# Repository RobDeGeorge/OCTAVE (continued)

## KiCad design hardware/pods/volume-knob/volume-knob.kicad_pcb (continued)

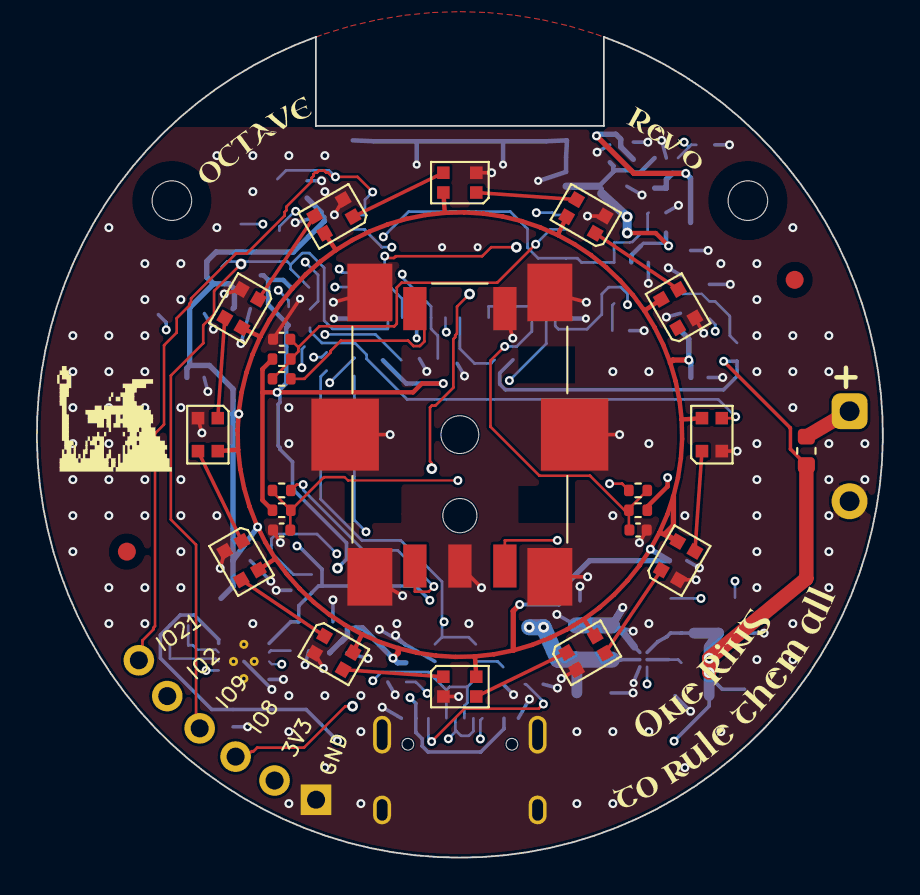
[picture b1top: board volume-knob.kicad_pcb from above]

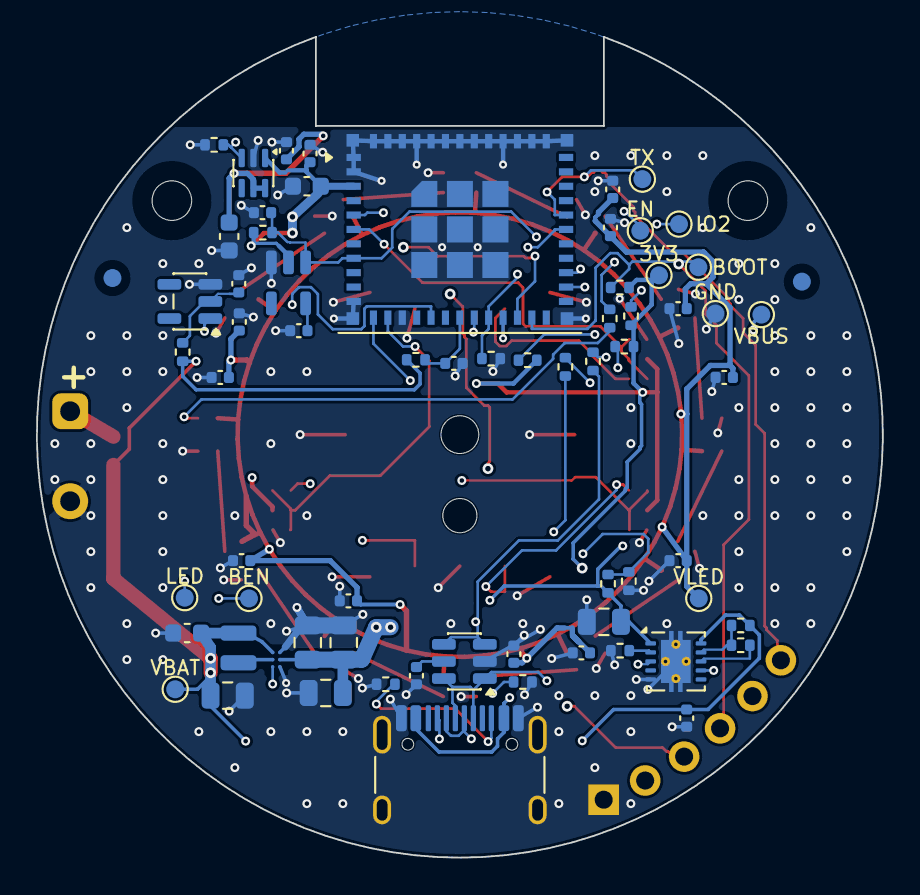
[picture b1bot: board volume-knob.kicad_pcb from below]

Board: 4 copper layers, 47.0 x 45.6 mm, 102 parts (75 on the bottom side), 49 nets.

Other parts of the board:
FID1, FID2, FID3, FID4: Fiducial_1mm_Mask2mm
H1, H2: M2; MountingHole_2.2mm_M2

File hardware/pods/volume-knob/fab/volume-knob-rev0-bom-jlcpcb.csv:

Comment,Designator,Footprint,LCSC
100n,"C1,C10,C13,C14,C19,C20,C21,C22,C23,C24,C25,C26,C27,C28,C29,C30",C_0402_1005Metric,C1525
4.7u,C2,C_0805_2012Metric,C1779
1u,"C3,C4",C_0402_1005Metric,C52923
10u,"C5,C11,C12",C_0603_1608Metric,C19702
22u,"C6,C7,C8,C9",C_0805_2012Metric,C45783
10n,"C15,C18",C_0402_1005Metric,C15195
220p,"C16,C17",C_0402_1005Metric,C1530
WS2812B-2020,"D1,D2,D3,D4,D5,D6,D7,D8,D9,D10,D11,D12",LED_WS2812B-2020_PLCC4_2.0x2.0mm,C52917434
3A,F1,Fuse_0603_1608Metric,C99558
USB-C,J1,USB_C_Receptacle_HRO_TYPE-C-31-M-12,C165948
1u,L1,L_Sunlord_SWPA252012S,C98348
5.1k,"R1,R2",R_0402_1005Metric,C25905
22,"R3,R4",R_0402_1005Metric,C25092
100k,"R5,R8,R10,R13",R_0402_1005Metric,C25741
150k,R6,R_0402_1005Metric,C25755
2k,R7,R_0402_1005Metric,C4109
200k,R9,R_0402_1005Metric,C25764
10k,"R11,R14,R15,R16,R17,R18",R_0402_1005Metric,C25744
470k,R12,R_0402_1005Metric,C25790
1k,"R19,R21,R23",R_0402_1005Metric,C11702
1M,"R20,R22",R_0402_1005Metric,C26083
33k,R24,R_0402_1005Metric,C25779
330,R25,R_0402_1005Metric,C25104
EC11J1525402,SW1,RotaryEncoder_Alps_EC11J15_SMD,C209762
USBLC6-2SC6,U1,SOT-23-6,C7519
BQ25173QWDRCRQ1,U2,Texas_DRC0010J_ThermalVias,C20345235
TPS3840PL16DBVR,U3,SOT-23-5,C1852124
TPS61299YBHR,U4,TI_YBH0006_WCSP-6_0.8x1.2mm,C20882919
TPS22919DCKR,U5,SOT-363_SC-70-6,C2149796
ESP32-C3-MINI-1-H4X,U6,ESP32-C3-MINI-1,C41349510
TPS3840DL28DBVR,U7,SOT-23-5,C2066416

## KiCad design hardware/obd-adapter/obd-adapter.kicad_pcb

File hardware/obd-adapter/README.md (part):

# OCTAVE OBD adapter, Rev 0 (bring-up board)

Our own OBD-II adapter: STM32G474 (vehicle side) + ESP32 (Bluetooth Classic SPP, BLE, Wi-Fi), every OBD-II bus, USB-C. Rev 0 is a bring-up board for the bench and the Jeep, not the final dongle. It has room to probe, test points and header access to spare pins, and it plugs straight into the car's OBD-II port. Plan and background: `TODO/diy-obd-adapter.md`.

**Status:** generated, then verified: an STM32 pin check against ST's pin data, two independent datasheet audits and ngspice simulations. Every finding is fixed or accepted, see `verify/REVIEW.md`. Not yet reviewed by a human, not ordered. Read "Before ordering" below.

**Compact two-sided board, after four design reviews (2026-11-24 and 25): routed, order files in `fab/`, not reviewed by a person, not ordered.** The board is **80 x 55 mm, six layers, parts on both sides** (74 on top, 144 underneath, 218 in all; 205 fitted by JLCPCB): 86 % of the area of the first compact pass (89 x 57.5 mm) and 60 % of the one-sided 100 x 70 mm board with its pod-bus lobe.

- **Routed and rule-checked:** 0 unconnected pads, 0 errors, schematic and board agree (ERC 0 / 0). Eight DRC warnings are left: silkscreen outlines over the board edge (the USB-C socket's twice, the module's once), U4's footprint differing from the library copy on purpose (1), and four vias KiCad calls dangling (each joins tracks of one layer; the clean-up step leaves any whose removal would open a net). `gen/routing.json` is this route and `build.py route` replays it.
- **Six layers** (F.Cu signal, In1 GND, In2 signal, In3 signal, In4 3V3, B.Cu signal). 292 signal vias of 0.45 / 0.2 mm, 305 of 0.6 / 0.3 mm. **Six layers and two-sided assembly cost more than Rev 0 would have; neither is priced.**
- **0402 for the logic-level resistors and small capacitors** (`HV_NETS` in `gen/obd_adapter.py` says which nets keep 0603: everything that can see the battery or a bus line, the buck's own parts, the 0.1 % divider, 4.7 µF and 10 µF). 0402 was estimated to get the board to 80 x 50 mm; it gets it to 80 x 55, because the chips, diodes, transistors and connectors are what fill the back, and 0402 shrinks none of them.
- **One USB-C port for both chips:** a hub (U18 CH334P, Y2), the CH340C (U14) with its auto-reset pair on the hub's second port; one RGB LED (D1) in place of three; the four ESP32 programming pads are gone.
- **Changed by the design review of 2026-11-24** (three reviews: circuit, copper, manufacturing; what each found is in the next section).
- **`fab/` is this board** (`build.py fab`, 2026-11-25): gerbers, BOM, placement file for both sides, and the plug adapter's gerbers with its anchoring holes. The placement file's angles are checked against JLCPCB's own footprints for all but the inductor (see "What an order still needs"); the route of 2026-11-25 (after the fourth review's changes) is itself not reviewed.
- **Not re-verified:** `verify/REVIEW.md`, the pin check and the simulations describe the Rev 0 layout and netlist. Nothing added on 2026-11-24 is simulated.
- **Sections below "Blocks"** partly still describe the Rev 0 layout: "Before ordering" and "Known Rev 0 limits" have not been rewritten for the compact board.

## Design review of 2026-11-24

Three independent reviews of the routed board (circuit against datasheets; the copper, measured; manufacturing and the plug joint). What they found and what was done:

**Fixed in the netlist**
- **USB ESD array's clamp pin (U2 pin 5) is on 3V3, not VBUS.** On VBUS, the hub's D+ pull-up fed the cable-less VBUS through the array: about 1 mA while parked, and enough on the ESP32 load switch's ON pin to turn the ESP32 on in a warm car.
- **Pod supply switch: U19 TPS27S100A** (HTSSOP-14) replaces the discrete P-FET switch (Q12, Q13, R71, D29 are gone; C52 and R72 have new jobs). It limits at 0.82 A (R72 3k; 0.59-1.05 A over tolerance and temperature), shuts down hot and retries. The P-FET would have burned in a shorted pod cable before the polyfuse tripped. **A shorted cable is survived, not free:** U19 then cycles at its thermal limit and draws about 0.2 A from the battery for as long as it is on, under the polyfuse's hold current, and its fault flag is not wired (no pin left). Firmware must switch `POD_EN` off when the pods stop answering and when the car is parked. U19 is rated 40 V, 48 V for 0.4 s.
- **Input TVS: 5.0SMDJ33CA** (it was 26CA). The 26 V part breaks down at 28.9-31.9 V, so it conducted through the whole of a clamped load dump (35 V, up to 0.4 s). The 33 V part starts at 36.7 V and clamps higher: about 42 V at 10 A and 46 V at 43 A at 25 °C, an estimated 49 to 50 V hot. That is at the rating of the 50 V capacitors and 1 to 2 V over U19's 48 V transient rating in the worst pulse in a hot car; accepted. **The LM317L (U11) is behind its own 30 V clamp** (Q15 BCX56-16 in SOT-89 as an emitter follower, D31 30 V zener, R80 1k): a firmware rule could not have protected it from a pulse that rises in a microsecond. The follower costs 0.7 to 1.5 V: Bus+ falls under VPW's 6.25 V when the plug is under about 9.0 V (10.8 V at worst, cold); without it 8.2 / 9.3 V. With Bus+ shorted while the adapter transmits, the LM317L's current limit flows through Q15, about 1 W: the SOT-89 takes that for a while, and **firmware must stop transmitting when `VPW_RX` does not echo the bus going high.** The comparator supply's resistor R43 is 1k (it was 470 Ω), so its 33 V zener stays inside its rating at the 41 V the TVS can let by for 0.4 s.
- **Q14: CONFIG switch 4 (BOOT0) also holds the ESP32 in reset,** and R78 holds the ESP32's TX line idle meanwhile. A USB cable powers the ESP32 by itself now, and one byte from it while the STM32's ROM bootloader picks its interface kept DFU from enumerating.
- **D30, a 5.1 V zener on the panic input:** the ESD diode alone lets PC13 reach 5 to 7 V with the cable shorted to the battery. R66 is 2k in 1206: 4.5 mA into the zener at 14.4 V (5.36 V at most), about 5.6 V at a 28 V jump start.
- **10 µF and 100 nF at the hub** (C55, C58): its low-voltage reset is 3.15 V at worst (datasheet V2.91: 2.6 / 3.0 / 3.15 V), the LDO 3.25 V before a load step, so the static margin is 100 mV; 3.15 V is also the hub's lowest operating voltage. **Check on the first board with Wi-Fi transmitting.** If the hub resets, it needs a small regulator of its own from 5V (its V5 pin cannot take 5V directly: on USB power that rail is 4.0 to 4.6 V, under the pin's 4.5 V minimum).

**Fixed in the copper** (`gen/prewire.py`, `gen/pcbgen.py`, `gen/build.py`)
- **`VBAT_P` leaves the ideal-diode FET on a 1.0 mm trunk** to the buck, the 10 µF and the 47 µF, with a via for the branches. Everything behind the FET had hung on the LM74700's 0.4 mm sense track and one via.
- **No fan-out via in a pad** (there were 20, under the STM32's pins and the accelerometer among them), none in a signal pin's way out of a fine-pitch chip, none in the USB-C shell's slot. The hub's centre pad has four vias in it on purpose, and about a dozen vias of a pad's own net stand 0.05 to 0.09 mm beside it (the buck's hand-laid ground vias, the module's ground pad, a few others). **Order the board with filled and capped vias.**
- **Beside the plug's hand-soldered pads:** no via and no pour within 0.45 mm of the pads on either side, no pour under the PTC, the PTC's battery pad 1.2 mm from the pads (0.65 before), 0.6 mm clearance round the unfused `VBAT_IN` copper (0.3 before).
- **Each CAN transceiver's 5 V capacitor is wired straight to its VCC pin;** the pod supply runs 0.6 mm on the outer layers (0.3 mm on an inner layer before); four ground vias under the hub; three to four more ground vias at the plug's ground pins, the TVS and the 47 µF.
- **No battery-side net on the top layer under the ESP32 module** (measured on this route: none).
- **The high-speed USB pair is laid by hand** (`gen/prewire.py`): socket, ESD array, hub, on B.Cu but for 2 mm at the socket, 21.5 and 22.0 mm long, three vias in all, the two lines 0.2 to 0.6 mm apart. Its impedance is not designed (0.15 mm tracks over the 3V3 plane, about 100 Ω differential by estimate). The STM32 is on the hub's port 3 now, so the upstream pins have their side of the chip alone.
- **Both CAN transceivers have their own 5 V feed** from the OR diode's anode, down In2 beside the feedback-sense trace, to a via at each one's 5 V capacitor. (The J1850 pull-up and reference divider, under 1 mA together, may still join the sense trace.)
- **The plug's two ground pins have four vias** on a short bus beside them, laid by hand; the LM317L's input capacitor is wired straight to its input pin; the pod switch's exposed pad has six vias into the ground plane; VBUS may use the inner layers (kept to the outer ones it ran 145 mm round the board); the pod output is 0.6 mm on the outer layers and the pod input 0.6 mm throughout (36 mm of it on an inner layer, where the finisher put it); the ESP32's supply pin has a via straight down to its 100 nF.
- **Track ends are welded** onto the track they join: the finisher had left 16 joints held only by overlapping round ends, narrower than a track.
- **The plug adapter board has two plated 0.45 mm holes in each joint pad,** at the end where pulling the plug out starts to peel it. (The main board's pads cannot have them: pin n and pin n + 8 are back to back.)

**Left as it is, on purpose or for now**
- **The joint still needs epoxy or a case that clamps the plug and the board.** The fillets were estimated to start lifting near 42 N; a J1962 plug takes 20 to 90 N to pull. Never pull the adapter out by its board. Treat the bead of epoxy along the joint as required.
- **The four buttons stand 5.7 mm apart:** a fingertip presses two. That is the price of the 80 mm length.
- **The battery-side clearance of 0.3 mm does not apply to `VJ1850` (7.2 V, regulated) and `K_IN` (behind 10k):** with it, the corner where the J1850 regulator stands over the comparator could not be wired.
- **The RGB LED's green and blue may be swapped:** its datasheet drawing has pin 3 green and pin 4 blue, as wired; JLCPCB's symbol for the same part number has them the other way round. A firmware swap if so.
- **The hub's D+ pull-up is always on** (the CH334P has no cable-detect pin): a cable to a powered-off host back-drives its D+ with up to 1.8 mA while parked.
- **The 3.3 V LDO** dissipates about 0.6 W with Wi-Fi sustained; in a hot car it may reach its thermal shutdown, which resets the board. Measure its tab on the first board.
- **The STM32 cannot tell that a USB cable is in** (no pin left): firmware polls, or stays attached at 0.1 mA from the battery.
- **Silkscreen outlines stand closer than 0.15 mm to their own part's pads** in about 300 places (the library's drawings); JLCPCB trims them.

## Design review of 2026-11-25 (fourth round)

Three more independent reviews (circuit, the copper of the route of that morning, the order package). No blocker in the circuit or the copper; one in the placement file. What was done:

- **Q15's placement angle was 180 degrees out** and its reel (C549696) had 4 pieces: it is the same part on the other reel now (C100026, BCX56-16,115) with its own correction. Every other part number's angle was confirmed against JLCPCB's footprint, J11 moved 0.25 mm.
- **The DLC switch is in the corner behind the buck's input,** under the copper it switches from: one via up into `VBAT_P`. It stood under the ESP32 module, and `VBAT_P` and `DLC_SW` crossed the board to it and back: 95 and 112 mm of battery-side track under the reset button, the STM32 and its crystal. The wizard has its old place.
- **Q15 has copper:** four vias in its collector tab to a patch on the top side (about 0.25 cm2, all there is room for). On the bare pad it was good for 0.5 W; the fault it has to stand (Bus+ shorted while transmitting) is 0.4 W typical, 1.4 W at worst. **Still a firmware obligation:** stop transmitting when `VPW_RX` does not echo.
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
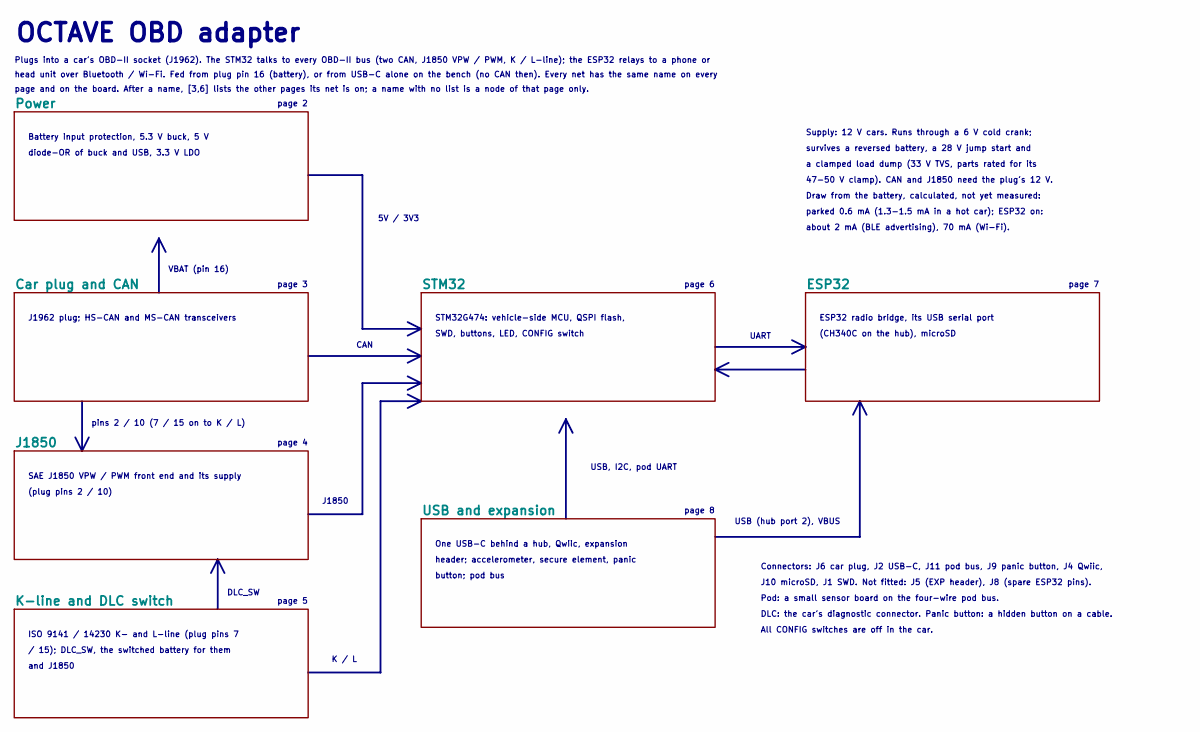
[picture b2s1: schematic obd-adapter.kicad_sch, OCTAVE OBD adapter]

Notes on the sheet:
page 2
Battery input protection, 5.3 V buck, 5 V
diode-OR of buck and USB, 3.3 V LDO
page 3
J1962 plug; HS-CAN and MS-CAN transceivers
page 4
SAE J1850 VPW / PWM front end and its supply
(plug pins 2 / 10)
page 5
ISO 9141 / 14230 K- and L-line (plug pins 7
/ 15); DLC_SW, the switched battery for them
and J1850
page 6
STM32G474: vehicle-side MCU, QSPI flash,
SWD, buttons, LED, CONFIG switch
page 7
ESP32 radio bridge, its USB serial port
(CH340C on the hub), microSD
page 8
One USB-C behind a hub, Qwiic, expansion
header; accelerometer, secure element, panic
button; pod bus
VBAT (pin 16)
5V / 3V3
CAN
J1850
K / L
UART
USB, I2C, pod UART
USB (hub port 2), VBUS
pins 2 / 10 (7 / 15 on to K / L)
DLC_SW
Connectors: J6 car plug, J2 USB-C, J11 pod bus, J9 panic button, J4 Qwiic,
J10 microSD, J1 SWD. Not fitted: J5 (EXP header), J8 (spare ESP32 pins).
Pod: a small sensor board on the four-wire pod bus.
DLC: the car's diagnostic connector. Panic button: a hidden button on a cable.
All CONFIG switches are off in the car.
Supply: 12 V cars. Runs through a 6 V cold crank;
survives a reversed battery, a 28 V jump start and
a clamped load dump (33 V TVS, parts rated for its

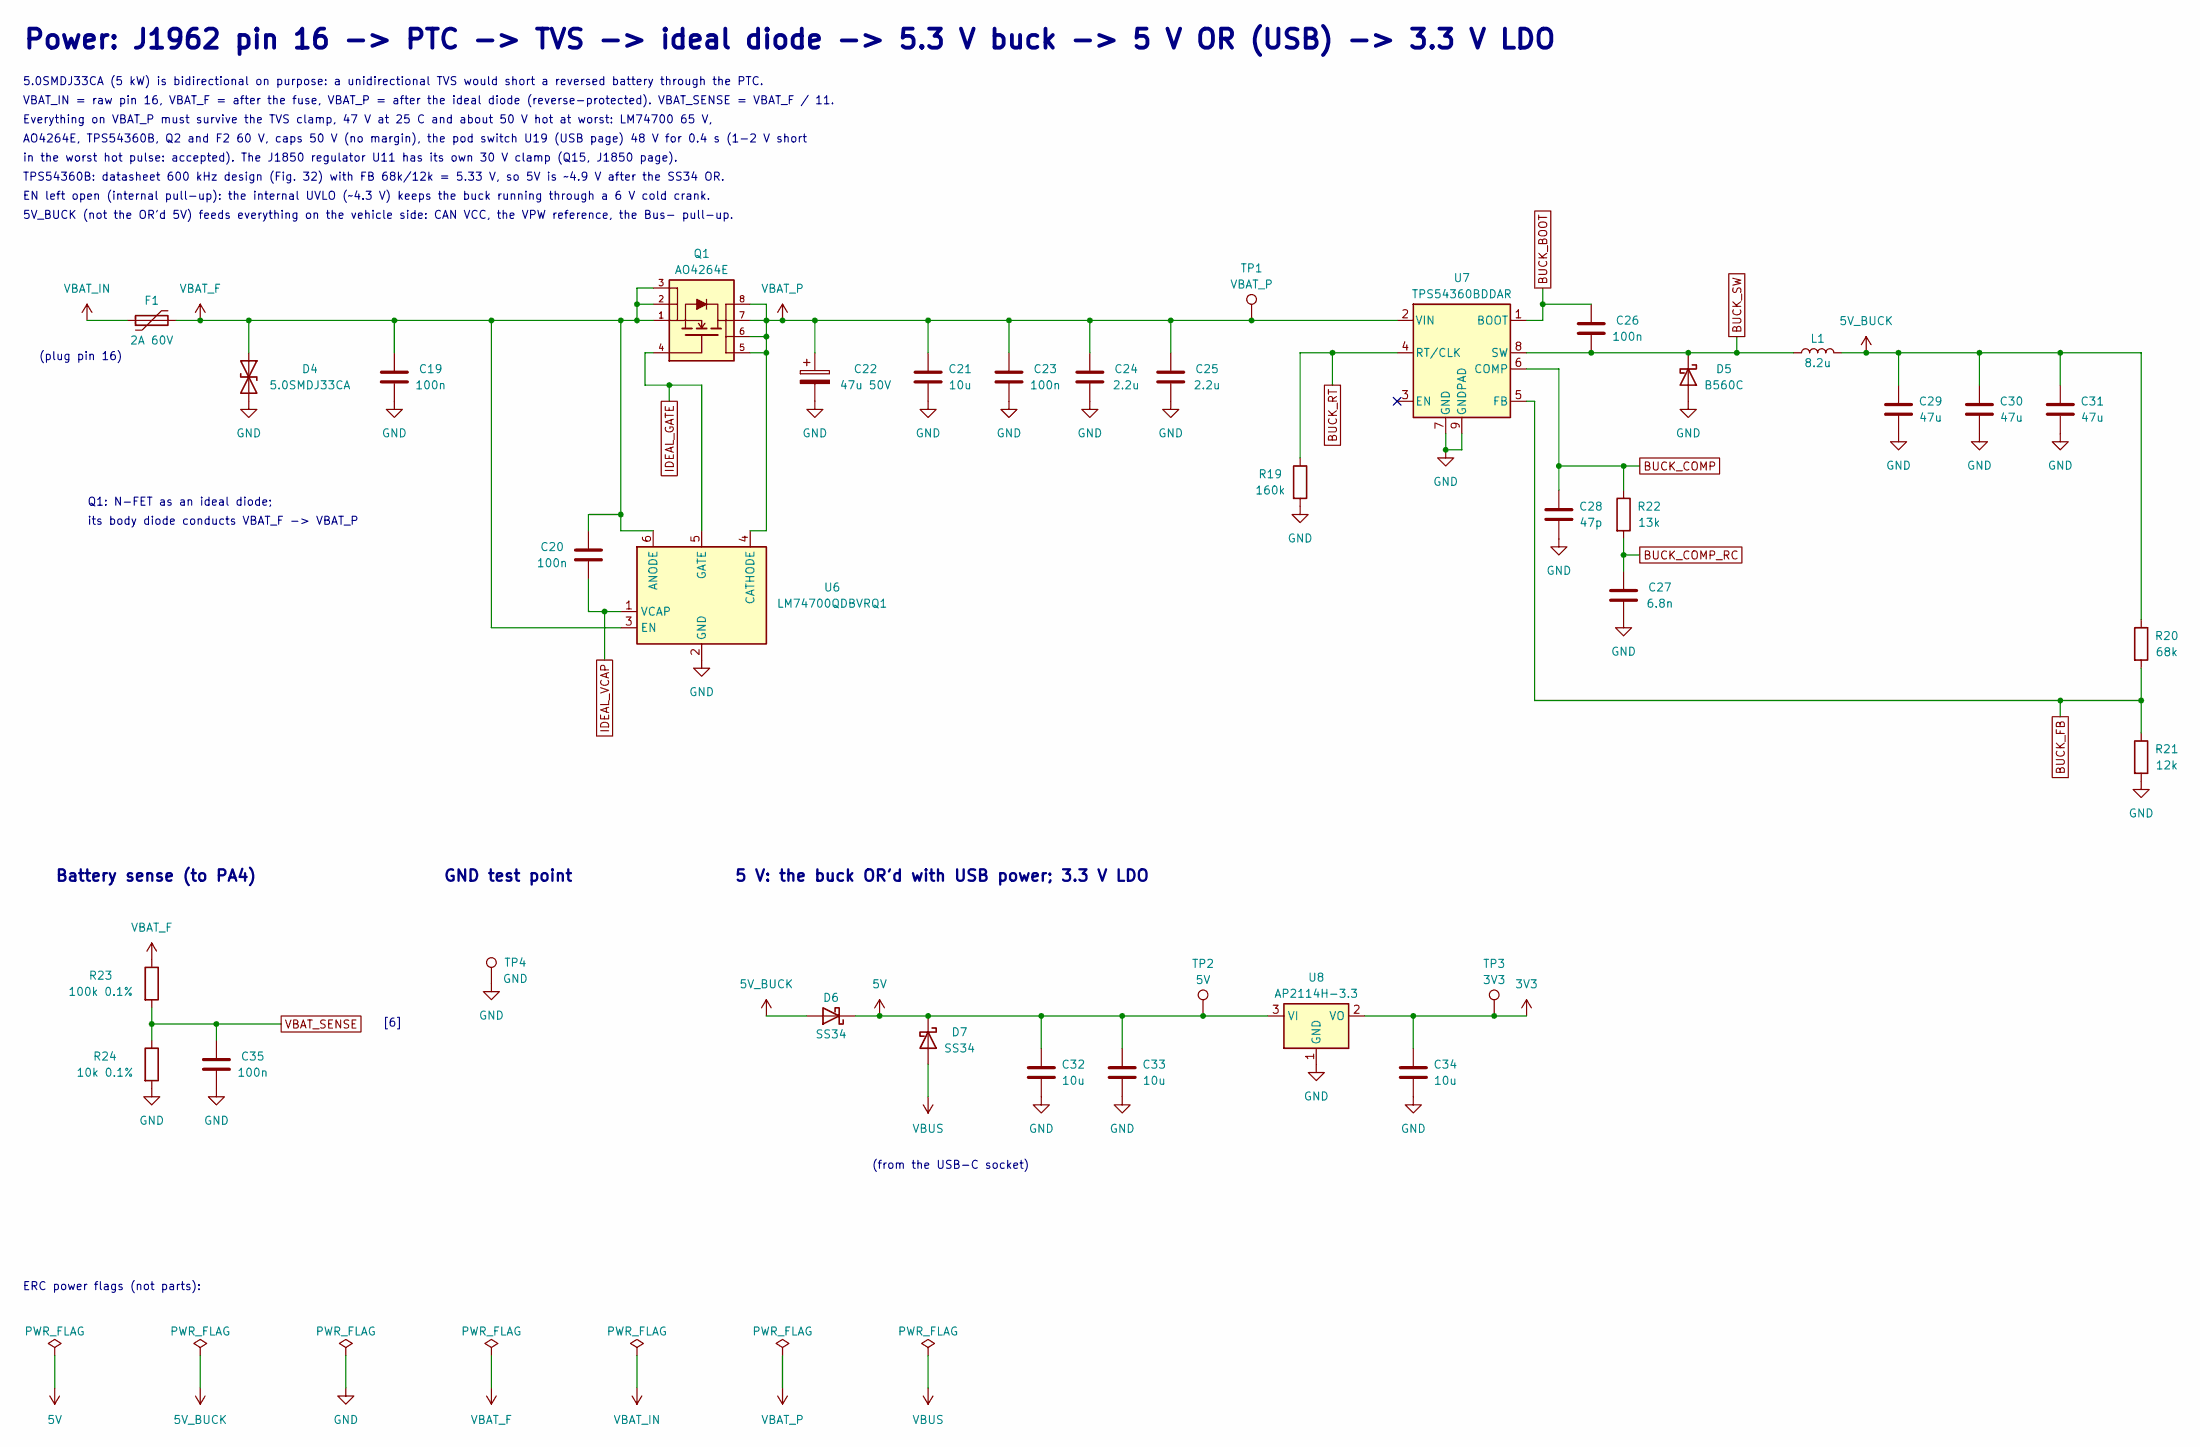
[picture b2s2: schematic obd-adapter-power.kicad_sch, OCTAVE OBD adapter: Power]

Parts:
C19, C20, C23, C26: 100n; C_0603_1608Metric; LCSC C14663
C21: 10u; C_1206_3216Metric; LCSC C13585
C22: 47u 50V; CP_Elec_6.3x7.7; LCSC C2887275
C24, C25: 2.2u; C_1206_3216Metric; LCSC C50254
C27: 6.8n; C_0603_1608Metric; LCSC C1631
C28: 47p; C_0603_1608Metric; LCSC C1671
C29, C30, C31: 47u; C_1206_3216Metric; LCSC C96123
C32, C33, C34: 10u; C_0603_1608Metric; LCSC C96446
C35: 100n; C_0402_1005Metric; LCSC C307331
D4: 5.0SMDJ33CA; D_SMC; LCSC C2913642
D5: B560C; D_SMC; LCSC C85100
D6, D7: SS34; D_SMA; LCSC C8678
F1: 2A 60V; Fuse_2920_7451Metric; LCSC C49326266
L1: 8.2u; L_Changjiang_FNR8065S; LCSC C96978
Q1: AO4264E; SOIC-8_3.9x4.9mm_P1.27mm; LCSC C334232
R19: 160k; R_0603_1608Metric; LCSC C22813
R20: 68k; R_0603_1608Metric; LCSC C23231
R21: 12k; R_0603_1608Metric; LCSC C22790
R22: 13k; R_0603_1608Metric; LCSC C22797
R23: 100k 0.1%; R_0603_1608Metric; LCSC C122538
R24: 10k 0.1%; R_0603_1608Metric; LCSC C95204
TP1: VBAT_P; TestPoint_Pad_D1.5mm
TP2: 5V; TestPoint_Pad_D1.5mm
TP3: 3V3; TestPoint_Pad_D1.5mm
TP4: GND; TestPoint_Pad_D1.5mm
U6: LM74700QDBVRQ1; SOT-23-6; LCSC C2941042
U7: TPS54360BDDAR; TI_SO-PowerPAD-8_ThermalVias; LCSC C524806
U8: AP2114H-3.3; SOT-223-3_TabPin2; LCSC C150716

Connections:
3V3: C34.1, TP3.1, U8.2 (VO); also elsewhere on the board
5V: C32.1, C33.1, D6.1 (K), D7.1 (K), TP2.1, U8.3 (VI); also elsewhere on the board
5V_BUCK: C29.1, C30.1, C31.1, D6.2 (A), L1.2, R20.1; also elsewhere on the board
BUCK_BOOT: C26.1, U7.1 (BOOT)
BUCK_COMP: C28.1, R22.1, U7.6 (COMP)
BUCK_COMP_RC: C27.1, R22.2
BUCK_FB: R20.2, R21.1, U7.5 (FB)
BUCK_RT: R19.1, U7.4 (RT/CLK)
BUCK_SW: C26.2, D5.1 (K), L1.1, U7.8 (SW)
GND: C19.2, C21.2, C22.2, C23.2, C24.2, C25.2, C27.2, C28.2, C29.2, C30.2, C31.2, C32.2, C33.2, C34.2, C35.2, D4.2 (A2), D5.2 (A), R19.2, R21.2, R24.2, TP4.1, U6.2 (GND), U7.7 (GND), U7.9 (GNDPAD), U8.1 (GND); also elsewhere on the board
IDEAL_GATE: Q1.4 (G), U6.5 (GATE)
IDEAL_VCAP: C20.1, U6.1 (VCAP)
VBAT_F: C19.1, C20.2, D4.1 (A1), F1.2, Q1.1 (S), Q1.2 (S), Q1.3 (S), R23.1, U6.3 (EN), U6.6 (ANODE)
VBAT_IN: F1.1; also elsewhere on the board
VBAT_P: C21.1, C22.1, C23.1, C24.1, C25.1, Q1.5 (D), Q1.6 (D), Q1.7 (D), Q1.8 (D), TP1.1, U6.4 (CATHODE), U7.2 (VIN); also elsewhere on the board
VBAT_SENSE: C35.1, R23.2, R24.1; also elsewhere on the board
VBUS: D7.2 (A); also elsewhere on the board

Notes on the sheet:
ERC power flags (not parts):
Power: J1962 pin 16 -> PTC -> TVS -> ideal diode -> 5.3 V buck -> 5 V OR (USB) -> 3.3 V LDO
5.0SMDJ33CA (5 kW) is bidirectional on purpose: a unidirectional TVS would short a reversed battery through the PTC.
VBAT_IN = raw pin 16, VBAT_F = after the fuse, VBAT_P = after the ideal diode (reverse-protected). VBAT_SENSE = VBAT_F / 11.
Everything on VBAT_P must survive the TVS clamp, 47 V at 25 C and about 50 V hot at worst: LM74700 65 V,
AO4264E, TPS54360B, Q2 and F2 60 V, caps 50 V (no margin), the pod switch U19 (USB page) 48 V for 0.4 s (1-2 V short
in the worst hot pulse: accepted). The J1850 regulator U11 has its own 30 V clamp (Q15, J1850 page).
TPS54360B: datasheet 600 kHz design (Fig. 32) with FB 68k/12k = 5.33 V, so 5V is ~4.9 V after the SS34 OR.
EN left open (internal pull-up): the internal UVLO (~4.3 V) keeps the buck running through a 6 V cold crank.
5V_BUCK (not the OR'd 5V) feeds everything on the vehicle side: CAN VCC, the VPW reference, the Bus- pull-up.
(plug pin 16)
Q1: N-FET as an ideal diode;
its body diode conducts VBAT_F -> VBAT_P
5 V: the buck OR'd with USB power; 3.3 V LDO
(from the USB-C socket)
Battery sense (to PA4)
GND test point
[6]

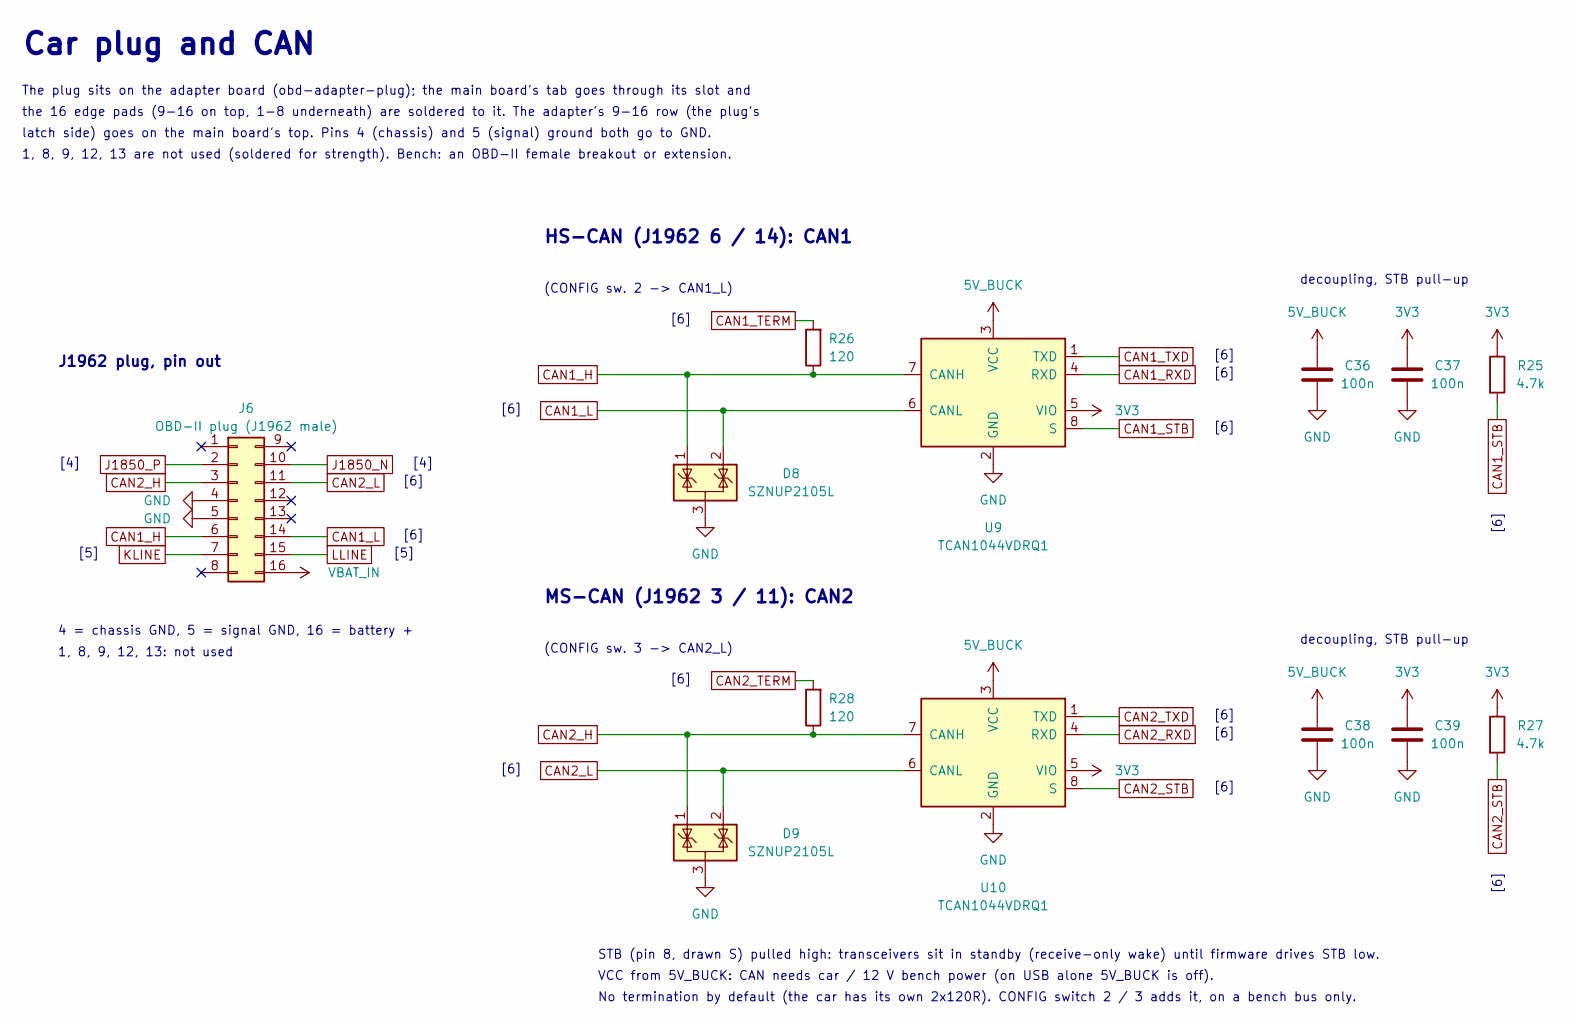
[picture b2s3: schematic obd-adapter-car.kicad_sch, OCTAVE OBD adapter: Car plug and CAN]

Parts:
C36, C37, C38, C39: 100n; C_0402_1005Metric; LCSC C307331
D8, D9: SZNUP2105L; SOT-23; LCSC C233494
J6: OBD-II plug (J1962 male); J1962_Edge_Joint
R25, R27: 4.7k; R_0402_1005Metric; LCSC C25900
R26, R28: 120; R_0603_1608Metric; LCSC C22787
U9, U10: TCAN1044VDRQ1; SOIC-8_3.9x4.9mm_P1.27mm; LCSC C1852061

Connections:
3V3: C37.1, C39.1, R25.1, R27.1, U9.5 (VIO), U10.5 (VIO); also elsewhere on the board
5V_BUCK: C36.1, C38.1, U9.3 (VCC), U10.3 (VCC); also elsewhere on the board
CAN1_H: D8.1 (K), J6.6, R26.1, U9.7 (CANH)
CAN1_L: D8.2 (K), J6.14, U9.6 (CANL); also elsewhere on the board
CAN1_RXD: U9.4 (RXD); also elsewhere on the board
CAN1_STB: R25.2, U9.8 (S); also elsewhere on the board
CAN1_TERM: R26.2; also elsewhere on the board
CAN1_TXD: U9.1 (TXD); also elsewhere on the board
CAN2_H: D9.1 (K), J6.3, R28.1, U10.7 (CANH)
CAN2_L: D9.2 (K), J6.11, U10.6 (CANL); also elsewhere on the board
CAN2_RXD: U10.4 (RXD); also elsewhere on the board
CAN2_STB: R27.2, U10.8 (S); also elsewhere on the board
CAN2_TERM: R28.2; also elsewhere on the board
CAN2_TXD: U10.1 (TXD); also elsewhere on the board
GND: C36.2, C37.2, C38.2, C39.2, D8.3 (A), D9.3 (A), J6.4, J6.5, U9.2 (GND), U10.2 (GND); also elsewhere on the board
J1850_N: J6.10; also elsewhere on the board
J1850_P: J6.2; also elsewhere on the board
KLINE: J6.7; also elsewhere on the board
LLINE: J6.15; also elsewhere on the board
VBAT_IN: J6.16; also elsewhere on the board

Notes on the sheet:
Car plug and CAN
The plug sits on the adapter board (obd-adapter-plug); the main board's tab goes through its slot and
the 16 edge pads (9-16 on top, 1-8 underneath) are soldered to it. The adapter's 9-16 row (the plug's
latch side) goes on the main board's top. Pins 4 (chassis) and 5 (signal) ground both go to GND.
1, 8, 9, 12, 13 are not used (soldered for strength). Bench: an OBD-II female breakout or extension.
J1962 plug, pin out
4 = chassis GND, 5 = signal GND, 16 = battery +
1, 8, 9, 12, 13: not used
HS-CAN (J1962 6 / 14): CAN1
(CONFIG sw. 2 -> CAN1_L)
decoupling, STB pull-up
MS-CAN (J1962 3 / 11): CAN2
(CONFIG sw. 3 -> CAN2_L)
STB (pin 8, drawn S) pulled high: transceivers sit in standby (receive-only wake) until firmware drives STB low.
VCC from 5V_BUCK: CAN needs car / 12 V bench power (on USB alone 5V_BUCK is off).
No termination by default (the car has its own 2x120R). CONFIG switch 2 / 3 adds it, on a bench bus only.
[4]
[5]
[6]

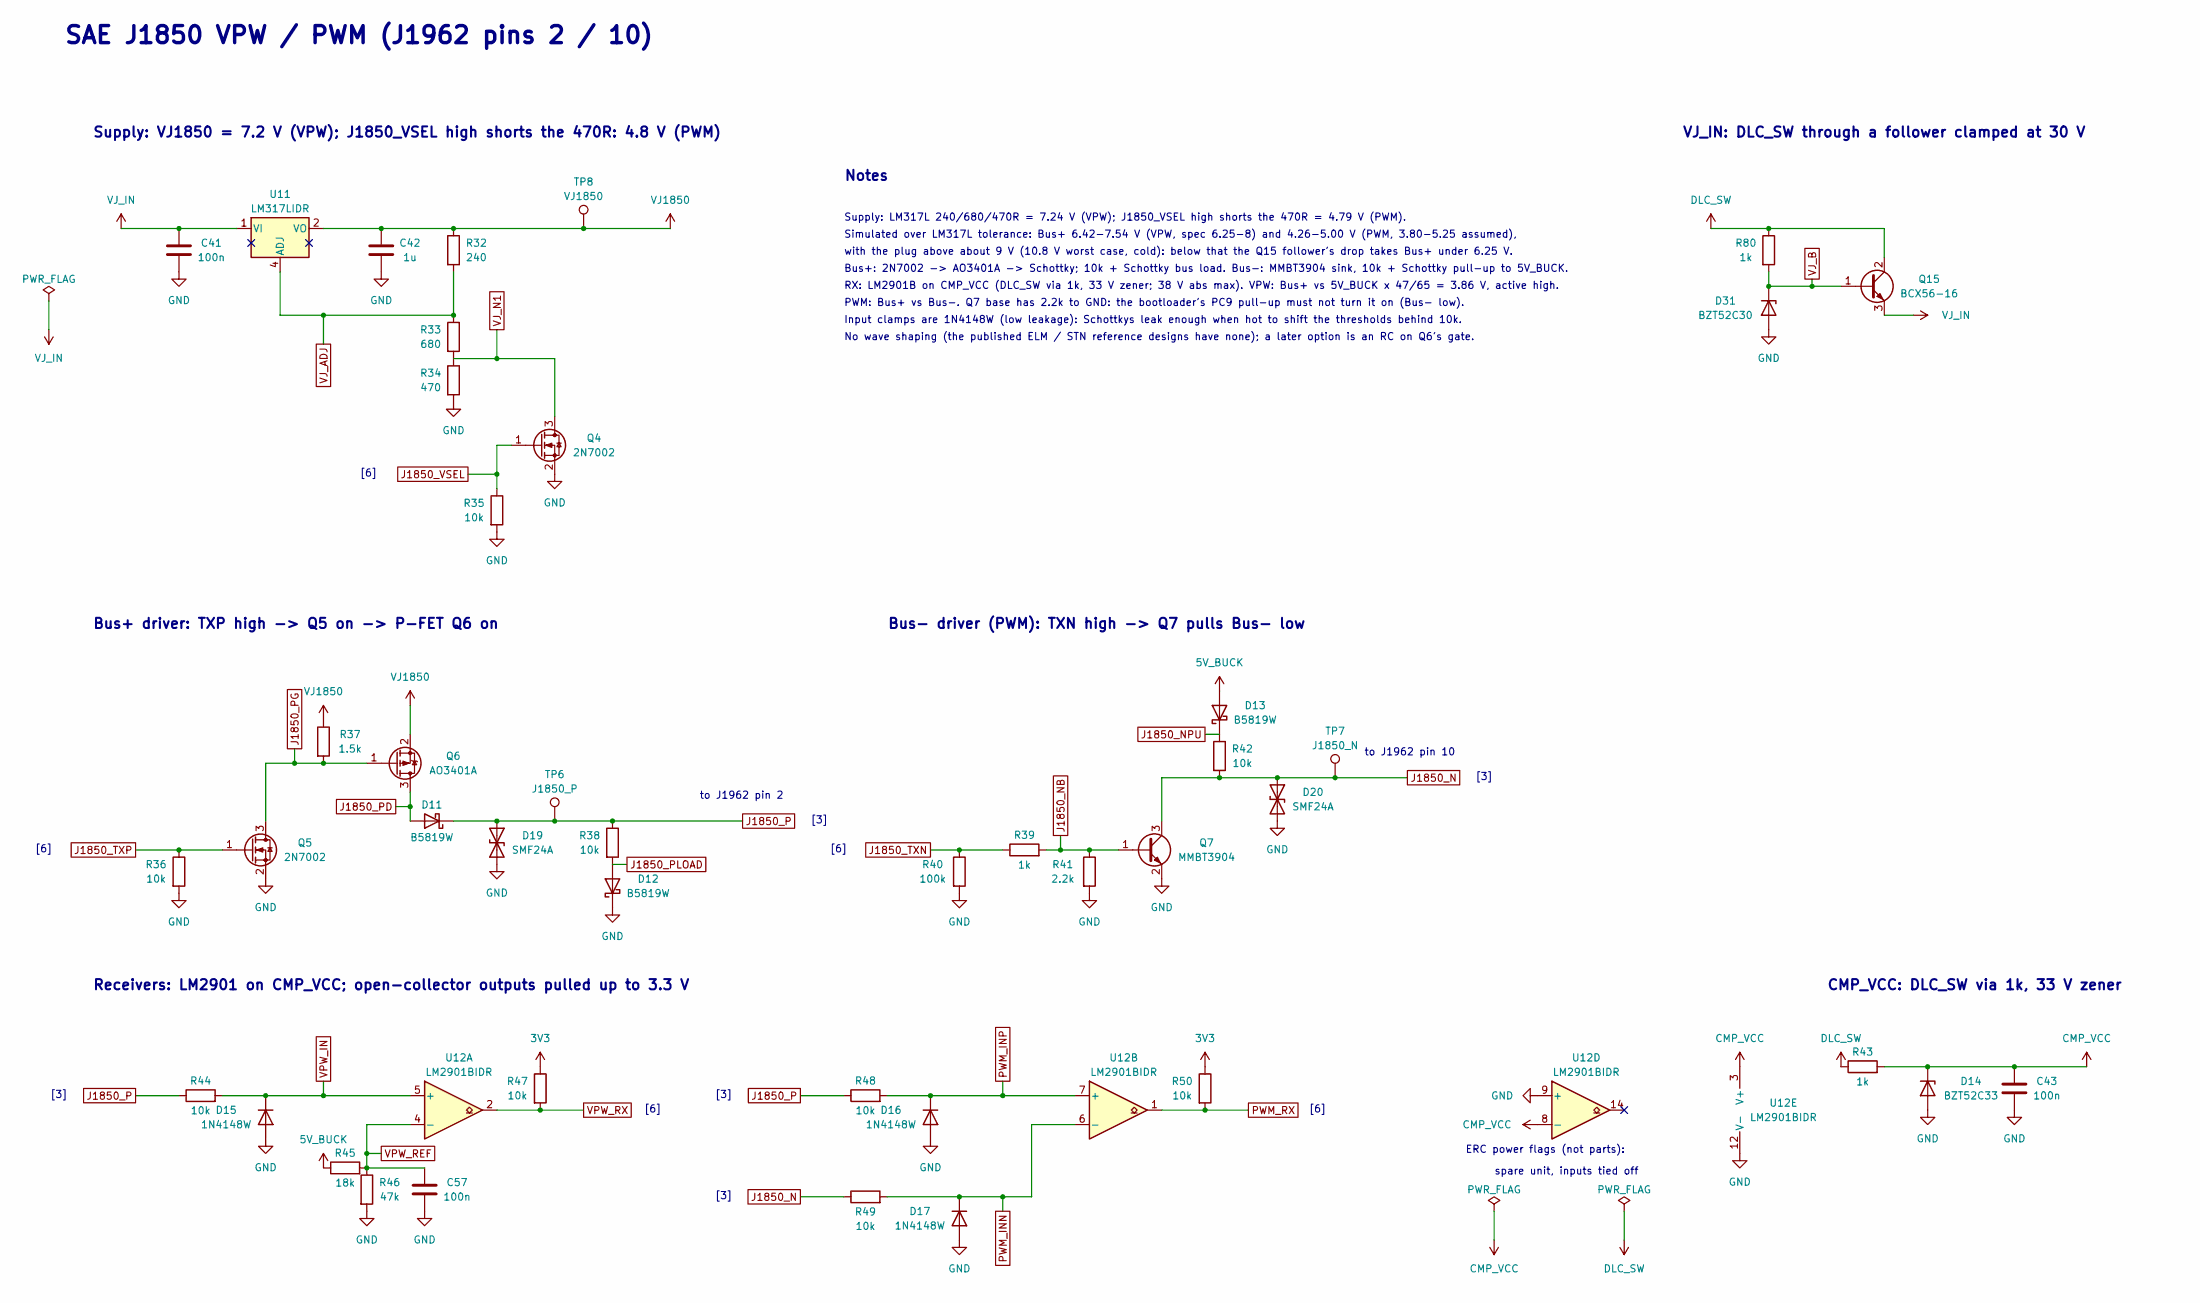
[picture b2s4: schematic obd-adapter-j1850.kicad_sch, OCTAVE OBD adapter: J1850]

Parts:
C41, C43: 100n; C_0603_1608Metric; LCSC C14663
C42: 1u; C_0603_1608Metric; LCSC C15849
C57: 100n; C_0402_1005Metric; LCSC C307331
D11, D12, D13: B5819W; D_SOD-123; LCSC C8598
D14: BZT52C33; D_SOD-123; LCSC C173417
D15, D16, D17: 1N4148W; D_SOD-123; LCSC C81598
D19, D20: SMF24A; D_SOD-123F; LCSC C19077514
D31: BZT52C30; D_SOD-123; LCSC C19077418
Q4, Q5: 2N7002; SOT-23; LCSC C8545
Q6: AO3401A; SOT-23; LCSC C15127
Q7: MMBT3904; SOT-23; LCSC C20526
Q15: BCX56-16; SOT-89-3; LCSC C100026
R32: 240; R_0603_1608Metric; LCSC C23350
R33: 680; R_0603_1608Metric; LCSC C23228
R34: 470; R_0603_1608Metric; LCSC C23179
R35, R36, R47, R50: 10k; R_0402_1005Metric; LCSC C25744
R37: 1.5k; R_0603_1608Metric; LCSC C22843
R38, R42, R44, R48, R49: 10k; R_0603_1608Metric; LCSC C25804
R39: 1k; R_0402_1005Metric; LCSC C11702
R40: 100k; R_0402_1005Metric; LCSC C25741
R41: 2.2k; R_0402_1005Metric; LCSC C25879
R43: 1k; R_1206_3216Metric; LCSC C4410
R45: 18k; R_0402_1005Metric; LCSC C25762
R46: 47k; R_0402_1005Metric; LCSC C25792
R80: 1k; R_0603_1608Metric; LCSC C21190
TP6: J1850_P; TestPoint_Pad_D1.5mm
TP7: J1850_N; TestPoint_Pad_D1.5mm
TP8: VJ1850; TestPoint_Pad_D1.5mm
U11: LM317LIDR; SOIC-8_3.9x4.9mm_P1.27mm; LCSC C183332
U12: LM2901BIDR; SOIC-14_3.9x8.7mm_P1.27mm; LCSC C22427890

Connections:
3V3: R47.1, R50.1; also elsewhere on the board
5V_BUCK: D13.2 (A), R45.1; also elsewhere on the board
CMP_VCC: C43.1, D14.1 (K), R43.2, U12.3 (V+), U12.8 (-)
DLC_SW: Q15.2 (C), R43.1, R80.1; also elsewhere on the board
GND: C41.2, C42.2, C43.2, C57.2, D12.1 (K), D14.2 (A), D15.2 (A), D16.2 (A), D17.2 (A), D19.2 (A2), D20.2 (A2), D31.2 (A), Q4.2 (S), Q5.2 (S), Q7.2 (E), R34.2, R35.2, R36.2, R40.2, R41.2, R46.2, U12.9 (+), U12.12 (V-); also elsewhere on the board
J1850_N: D20.1 (A1), Q7.3 (C), R42.2, R49.1, TP7.1; also elsewhere on the board
J1850_NB: Q7.1 (B), R39.2, R41.1
J1850_NPU: D13.1 (K), R42.1
J1850_P: D11.1 (K), D19.1 (A1), R38.1, R44.1, R48.1, TP6.1; also elsewhere on the board
J1850_PD: D11.2 (A), Q6.3 (D)
J1850_PG: Q5.3 (D), Q6.1 (G), R37.2
J1850_PLOAD: D12.2 (A), R38.2
J1850_TXN: R39.1, R40.1; also elsewhere on the board
J1850_TXP: Q5.1 (G), R36.1; also elsewhere on the board
J1850_VSEL: Q4.1 (G), R35.1; also elsewhere on the board
PWM_INN: D17.1 (K), R49.2, U12.6 (-)
PWM_INP: D16.1 (K), R48.2, U12.7 (+)
PWM_RX: R50.2, U12.1; also elsewhere on the board
VJ1850: C42.1, Q6.2 (S), R32.1, R37.1, TP8.1, U11.2 (VO), U11.3 (VO), U11.6 (VO), U11.7 (VO)
VJ_ADJ: R32.2, R33.1, U11.4 (ADJ)
VJ_B: D31.1 (K), Q15.1 (B), R80.2
VJ_IN: C41.1, Q15.3 (E), U11.1 (VI)
VJ_N1: Q4.3 (D), R33.2, R34.1
VPW_IN: D15.1 (K), R44.2, U12.5 (+)
VPW_REF: C57.1, R45.2, R46.1, U12.4 (-)
VPW_RX: R47.2, U12.2; also elsewhere on the board

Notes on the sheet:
ERC power flags (not parts):
SAE J1850 VPW / PWM (J1962 pins 2 / 10)
Supply: VJ1850 = 7.2 V (VPW); J1850_VSEL high shorts the 470R: 4.8 V (PWM)
VJ_IN: DLC_SW through a follower clamped at 30 V
Bus+ driver: TXP high -> Q5 on -> P-FET Q6 on
to J1962 pin 2
Bus- driver (PWM): TXN high -> Q7 pulls Bus- low
to J1962 pin 10
Receivers: LM2901 on CMP_VCC; open-collector outputs pulled up to 3.3 V
spare unit, inputs tied off
CMP_VCC: DLC_SW via 1k, 33 V zener
Notes
Supply: LM317L 240/680/470R = 7.24 V (VPW); J1850_VSEL high shorts the 470R = 4.79 V (PWM).
Simulated over LM317L tolerance: Bus+ 6.42-7.54 V (VPW, spec 6.25-8) and 4.26-5.00 V (PWM, 3.80-5.25 assumed),
with the plug above about 9 V (10.8 V worst case, cold): below that the Q15 follower's drop takes Bus+ under 6.25 V.
Bus+: 2N7002 -> AO3401A -> Schottky; 10k + Schottky bus load. Bus-: MMBT3904 sink, 10k + Schottky pull-up to 5V_BUCK.
RX: LM2901B on CMP_VCC (DLC_SW via 1k, 33 V zener; 38 V abs max). VPW: Bus+ vs 5V_BUCK x 47/65 = 3.86 V, active high.
PWM: Bus+ vs Bus-. Q7 base has 2.2k to GND: the bootloader's PC9 pull-up must not turn it on (Bus- low).
Input clamps are 1N4148W (low leakage): Schottkys leak enough when hot to shift the thresholds behind 10k.
No wave shaping (the published ELM / STN reference designs have none); a later option is an RC on Q6's gate.
[6]
[3]

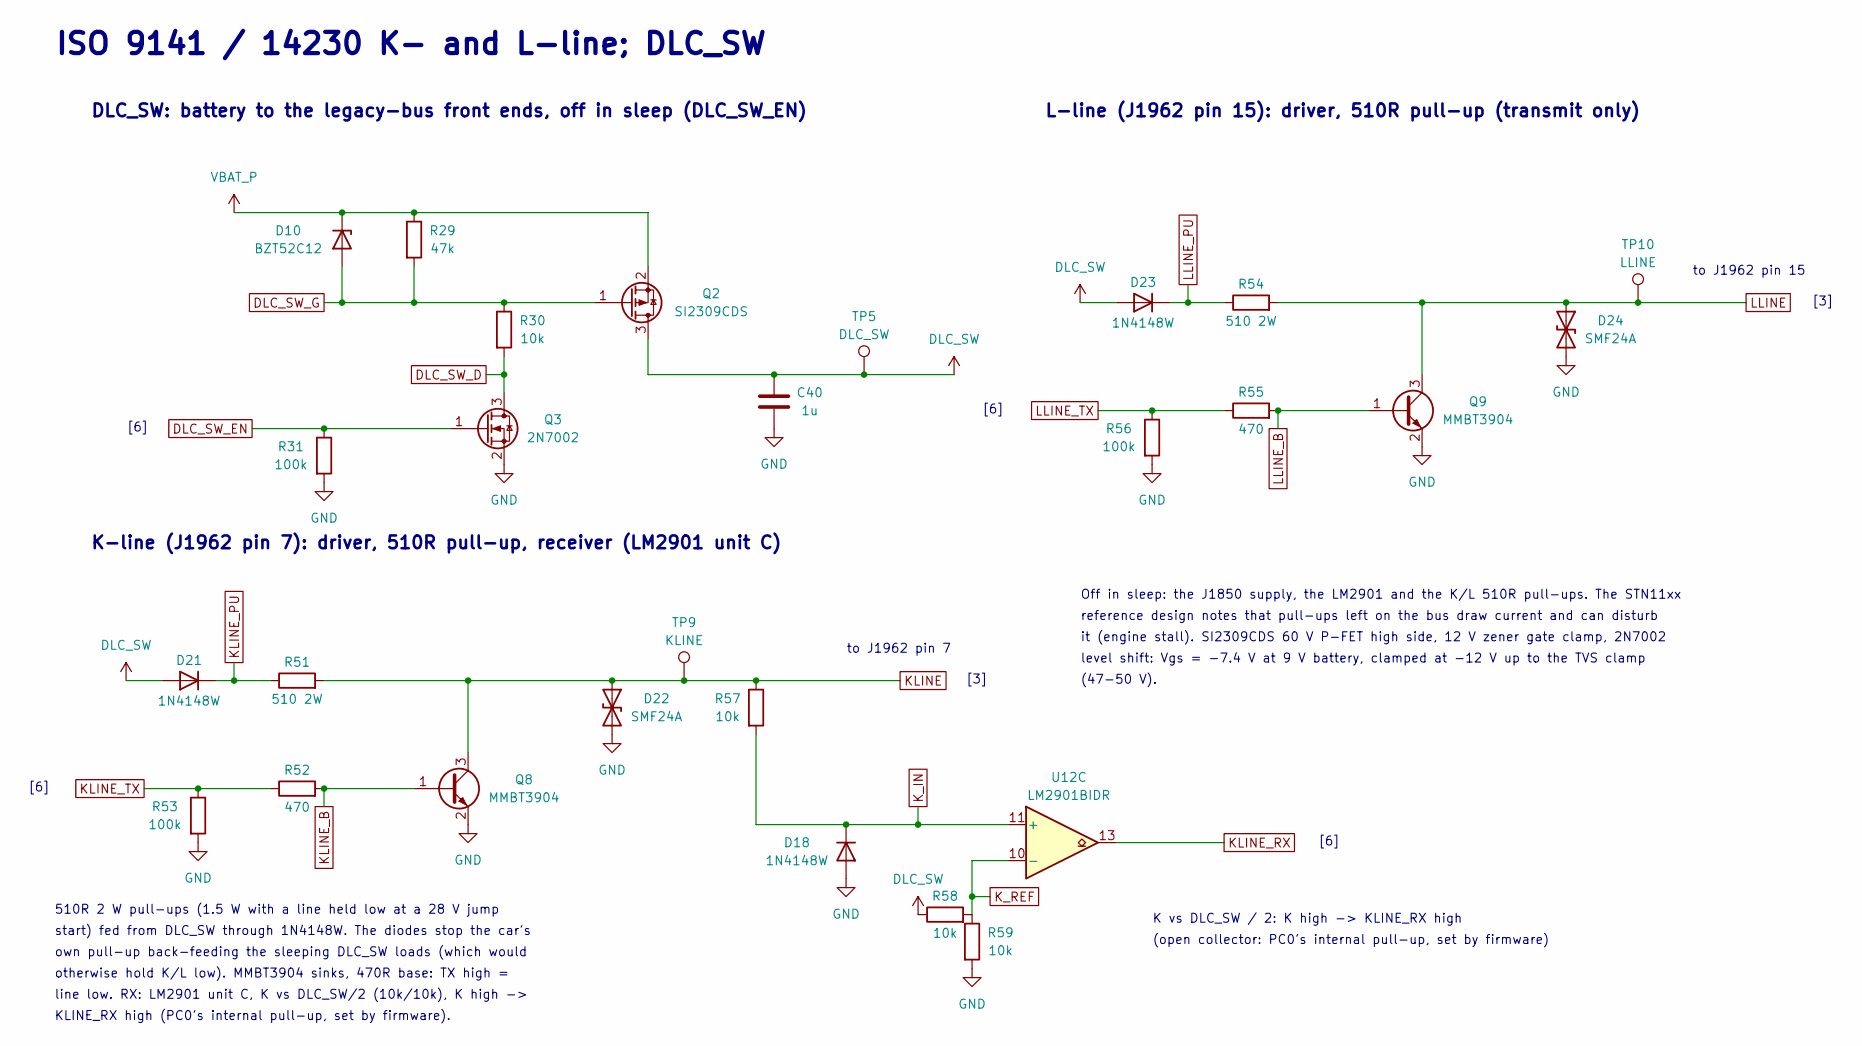
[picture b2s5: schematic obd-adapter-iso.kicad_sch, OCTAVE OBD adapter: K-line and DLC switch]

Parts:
C40: 1u; C_0603_1608Metric; LCSC C15849
D10: BZT52C12; D_SOD-123; LCSC C19077410
D18, D21, D23: 1N4148W; D_SOD-123; LCSC C81598
D22, D24: SMF24A; D_SOD-123F; LCSC C19077514
Q2: SI2309CDS; SOT-23; LCSC C10493
Q3: 2N7002; SOT-23; LCSC C8545
Q8, Q9: MMBT3904; SOT-23; LCSC C20526
R29: 47k; R_0603_1608Metric; LCSC C25819
R30, R57, R58, R59: 10k; R_0603_1608Metric; LCSC C25804
R31, R53, R56: 100k; R_0402_1005Metric; LCSC C25741
R51, R54: 510 2W; R_2512_6332Metric; LCSC C5843118
R52, R55: 470; R_0402_1005Metric; LCSC C25117
TP5: DLC_SW; TestPoint_Pad_D1.5mm
TP9: KLINE; TestPoint_Pad_D1.5mm
TP10: LLINE; TestPoint_Pad_D1.5mm
U12: LM2901BIDR; SOIC-14_3.9x8.7mm_P1.27mm; LCSC C22427890

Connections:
DLC_SW: C40.1, D21.2 (A), D23.2 (A), Q2.3 (D), R58.1, TP5.1; also elsewhere on the board
DLC_SW_D: Q3.3 (D), R30.2
DLC_SW_EN: Q3.1 (G), R31.1; also elsewhere on the board
DLC_SW_G: D10.2 (A), Q2.1 (G), R29.2, R30.1
GND: C40.2, D18.2 (A), D22.2 (A2), D24.2 (A2), Q3.2 (S), Q8.2 (E), Q9.2 (E), R31.2, R53.2, R56.2, R59.2; also elsewhere on the board
KLINE: D22.1 (A1), Q8.3 (C), R51.2, R57.1, TP9.1; also elsewhere on the board
KLINE_B: Q8.1 (B), R52.2
KLINE_PU: D21.1 (K), R51.1
KLINE_RX: U12.13; also elsewhere on the board
KLINE_TX: R52.1, R53.1; also elsewhere on the board
K_IN: D18.1 (K), R57.2, U12.11 (+)
K_REF: R58.2, R59.1, U12.10 (-)
LLINE: D24.1 (A1), Q9.3 (C), R54.2, TP10.1; also elsewhere on the board
LLINE_B: Q9.1 (B), R55.2
LLINE_PU: D23.1 (K), R54.1
LLINE_TX: R55.1, R56.1; also elsewhere on the board
VBAT_P: D10.1 (K), Q2.2 (S), R29.1; also elsewhere on the board

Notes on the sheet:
ISO 9141 / 14230 K- and L-line; DLC_SW
DLC_SW: battery to the legacy-bus front ends, off in sleep (DLC_SW_EN)
K-line (J1962 pin 7): driver, 510R pull-up, receiver (LM2901 unit C)
to J1962 pin 7
K vs DLC_SW / 2: K high -> KLINE_RX high
(open collector: PC0's internal pull-up, set by firmware)
L-line (J1962 pin 15): driver, 510R pull-up (transmit only)
to J1962 pin 15
510R 2 W pull-ups (1.5 W with a line held low at a 28 V jump
start) fed from DLC_SW through 1N4148W. The diodes stop the car's
own pull-up back-feeding the sleeping DLC_SW loads (which would
otherwise hold K/L low). MMBT3904 sinks, 470R base: TX high =
line low. RX: LM2901 unit C, K vs DLC_SW/2 (10k/10k), K high ->
KLINE_RX high (PC0's internal pull-up, set by firmware).
Off in sleep: the J1850 supply, the LM2901 and the K/L 510R pull-ups. The STN11xx
reference design notes that pull-ups left on the bus draw current and can disturb
it (engine stall). SI2309CDS 60 V P-FET high side, 12 V zener gate clamp, 2N7002
level shift: Vgs = -7.4 V at 9 V battery, clamped at -12 V up to the TVS clamp
(47-50 V).
[6]
[3]
